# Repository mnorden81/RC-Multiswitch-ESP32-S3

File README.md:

# RC-Multiswitch-ESP32-S3

RC-Multiswitch mit 8 Schaltkanaelen auf einem Waveshare ESP32-S3-Zero.

Frueher `CRSF-Multiswitch-ESP32-S3`. Der neue Name ist neutral, weil der Multiswitch neben CRSF auch SBUS (UART A) als Eingang versteht.

Gleiche Funktion wie die C3-Variante, aber mit dem ESP32-S3-Zero und einem dritten UART. Das PCB wurde vom C3-Layout uebernommen, die Leitungen am ESP32 sind neu verlegt (DRC steht noch aus).

Dokumente:
- [docs/Projektbeschreibung.docx](docs/Projektbeschreibung.docx): Projektbeschreibung
- [docs/Hardware-Beschreibung_C3_S3.docx](docs/Hardware-Beschreibung_C3_S3.docx): Hardware-Beschreibung C3 und S3 (Stecker, Kanalzuordnung, Stueckliste, Dimensionierung)
- [docs/Abnahmepruefung.md](docs/Abnahmepruefung.md): Abnahmepruefung (Pruefliste fuer ein fertig gebautes Modul)
- [docs/Firmware-Spezifikation.md](docs/Firmware-Spezifikation.md) (auch als DOCX): Firmware-Spezifikation (Basis V3, Router fuer Modulketten, BOOT-Taster, Status-LED)

## Merkmale
- 8 Schaltkanaele ueber TBD62083APG (negativ) oder TBD62783APG (positiv), Kontroll-LED je Kanal
- UART A (Eingang), UART B und UART C mit waehlbarer Rolle: Modulkette (CRSF), S.Port-LiPo-Sensoren, GPS oder Raw, je mit eigener Baudrate
- Versorgung des ESP32 aus +5 V des Empfaengers, Last getrennt mit 5-12 V
- Eigener THT-Footprint fuer den S3-Zero (nur 2x9 Header)

## Hardware (v0.4 (PCB vom C3 uebertragen))
Board: Waveshare ESP32-S3-Zero

- Lastspannung 5-12 V (VLOAD) an CN2 (JST PH 2), TVS-Diode P6KE18A als Schutz.
- Treiber TBD62083APG (DMOS, Nachfolger des ULN2803A, gleiche Pinbelegung; ein ULN2803A passt weiterhin in den Sockel), 8 Kanaele, max. 500 mA je Kanal, Summe aller Kanaele ca. 1,5 A. Spannungsabfall am Ausgang nur ca. 0,2-0,4 V statt ca. 1 V beim ULN2803A. Positiv schaltende Variante mit TBD62783APG siehe [hardware/README-hardware.md](hardware/README-hardware.md).
- R9-R16 (THT 1/4 W) zwischen Treiber-Ausgang und Stiftleiste J1: kein Wert vorgegeben, der Anwender legt sie passend zu Verbraucher und Lastspannung aus.
- R1-R8 und LED1-LED8 (3 mm) als Kontroll-LED je Kanal, vom Steuersignal Sn gegen GND. Werte legt der Anwender fest, eine Empfehlung ist auf der Platine aufgedruckt.
- Keine Pulldowns und keine Widerstaende in den UART-Leitungen. Der ESP32 wird aus +5 V von CN1 (BEC/Empfaenger) versorgt.

### Belegung
| Funktion | GPIO |
|---|---|
| S0..S7 | IO11, IO4, IO5, IO6, IO10, IO9, IO8, IO7 |
| UART A (CN1, Eingang) | TX IO43, RX IO44 (UART0) |
| UART B (J5) | TX IO13, RX IO12 |
| UART C (J6) | TX IO2, RX IO1 |
| Frei | IO3 (Strapping), IO14-IO16 (Loetpads) |

### Anschluesse
- CN1, J5, J6: UART A/B/C als JST-GH 4 (Footprint BM04B-GHS-TBT)
- CN2 Last 5-12 V (JST PH 2, max. ca. 2 A je Kontakt)
- J1 Ausgaenge S0..S7

### Hinweise
- UART A liegt auf UART0: beim Booten gibt das ROM ein Log auf IO43 aus.
- Empfehlung LED-Vorwiderstaende R1-R8 bei 3,3 V (ca. 5 mA, auch auf der Platine aufgedruckt): Rot/Gelb 270 R, Gruen 220 R, Blau/Weiss 56 R.
- Footprint ESP32-S3-Zero_THT: 2x9, 2,54 mm, Reihenabstand 15,24 mm. Vor dem Layout 1:1 am echten Board pruefen.

## Firmware (v4.09)
- Arduino-Sketch `firmware/RC_Multiswitch`, gleicher Quellcode fuer C3 und S3 (Board wird automatisch erkannt). Basis: MultiSwitch_ESP32_V3 v3.12.
- CRSF auf UART A (Werkseinstellung ab v4.07), wahlweise SBUS. UART B und UART C per Lua oder Web-UI auf Aus, CRSF (Modulkette), S.Port, GPS oder Raw einstellbar, mit eigener Baudrate je UART. Beim GPS sucht die Baudrate „Auto“ (Vorgabe) die Rate selbst und stellt das GPS auf 115200 Baud und 10 Hz um, wie bei Betaflight. In der Modulkette ist jedes Modul mit eigener Adresse ueber Lua einzeln einstellbar. Lua-Menü ab v4.09: Ordner zeigen ihren Wert (z. B. „Ausgang 1 (Kanal_L 5)“), Felder ohne Wirkung werden ausgeblendet.
- Gemeinsame Basis aller ESP32-Module seit v4.05: `firmware/RC_Multiswitch/src/RC_Common/` (siehe deren README).
- BOOT-Taster 3 s: WLAN-AP ein/aus. Status-LED nur beim S3.
- Details und Bauanleitung: [firmware/README.md](firmware/README.md).

## Firmware flashen

Es gibt drei Wege. Ein neues Modul wird einmal per USB geflasht (Weg 1 oder Weg 2), danach geht jedes Update bequem per WLAN (Weg 3).

| Weg | Braucht | Einstellungen im Modul |
|---|---|---|
| 1. Fertige Datei aus GitHub + Web-Flasher | nur Chrome oder Edge | werden **gelöscht** |
| 2. Arduino IDE | Arduino IDE 2.x | bleiben erhalten |
| 3. Update per WLAN | Handy oder PC mit WLAN | bleiben erhalten |

Der Sketch ist für C3 und S3 derselbe, das Board wird automatisch erkannt. Für dieses Repo (Waveshare ESP32-S3-Zero) gilt das Artefakt `RC_Multiswitch-S3` und die Einstellungen unten.

### Weg 1: Fertige Firmware aus GitHub (ohne Arduino IDE)

GitHub baut die Firmware bei jeder Änderung automatisch (Workflow „Firmware bauen“).

1. Auf GitHub angemeldet sein (sonst gibt es keinen Download-Knopf).
2. In diesem Repo oben auf **Actions** klicken, links den Workflow **Firmware bauen** wählen.
3. Den obersten Lauf mit grünem Haken öffnen (Branch `main`).
4. Ganz unten unter **Artifacts** **RC_Multiswitch-S3** herunterladen und die ZIP-Datei entpacken. Darin liegen u. a. `RC_Multiswitch.ino.merged.bin` (Komplett-Image für USB) und `RC_Multiswitch.ino.bin` (nur für Weg 3).
   Steht dort nichts (Artefakte werden nach 90 Tagen gelöscht): rechts oben **Run workflow** → **Run workflow** klicken, nach ca. 3 Minuten ist ein neuer Lauf fertig.
5. ESP32-S3-Zero mit einem USB-C-**Datenkabel** an den PC stecken (kein reines Ladekabel). Ein Treiber ist unter Windows 10/11 nicht nötig.
6. In **Chrome** oder **Edge** die Seite https://espressif.github.io/esptool-js/ öffnen (Espressif-Web-Flasher, Firefox geht nicht).
7. **Connect** klicken und den COM-Port des Moduls wählen. Klappt das nicht: Baudrate oben auf `115200` stellen und das Modul mit der BOOT-Taste in den Flash-Modus bringen (siehe Weg 2, „Wenn das Hochladen nicht klappt“).
8. Unter **Flash Address** `0x0` eintragen, mit **Datei auswählen** die `.merged.bin` wählen, dann **Program** klicken.
9. Wenn unten „Leaving…“ steht, das USB-Kabel kurz abziehen und wieder einstecken. Fertig.

> **Achtung:** Das Komplett-Image überschreibt den ganzen Flash (4 MB). Alle Einstellungen und die Sicherungen im Flash sind danach weg. Vorher in der Weboberfläche die Einstellungen als Datei sichern (Karte **Konfiguration sichern/wiederherstellen** → „Als Datei exportieren“) und hinterher dort wieder importieren. Wer die Einstellungen behalten will, nimmt Weg 2 oder 3.

### Weg 2: Arduino IDE

**Einmalig einrichten**

1. Arduino IDE 2.x installieren (https://www.arduino.cc/en/software).
2. **Datei → Einstellungen → Zusätzliche Boardverwalter-URLs**: `https://espressif.github.io/arduino-esp32/package_esp32_index.json` eintragen.
3. **Werkzeuge → Board → Boardverwalter**: „esp32“ suchen, **esp32 von Espressif Systems** in Version **3.0.7** installieren.
4. **Werkzeuge → Bibliotheken verwalten**: **Bolder Flight Systems SBUS 8.1.4**, **TinyGPSPlus 1.0.3** suchen und in genau dieser Version installieren.
   Alles andere (z. B. `src/RC_Common/`) liegt schon im Sketch-Ordner.

**Flashen**

1. Repo herunterladen: oben auf GitHub **Code → Download ZIP**, entpacken (oder den vorhandenen Ordner nehmen).
2. In der Arduino IDE **Datei → Öffnen** und `firmware/RC_Multiswitch/RC_Multiswitch.ino` wählen.
3. Unter **Werkzeuge** einstellen:

   | Einstellung | Wert |
   |---|---|
   | Board | **ESP32S3 Dev Module** |
   | USB CDC On Boot | **Enabled** (Pflicht, sonst Abbruch mit Meldung) |
   | Flash Size | 4MB (32Mb) |
   | Partition Scheme | **Default 4MB with spiffs (1.2MB APP/1.5MB SPIFFS)** |
   | PSRAM | Disabled |
   | Erase All Flash Before Sketch Upload | **Disabled** (sonst sind die Einstellungen weg) |

4. ESP32-S3-Zero mit einem USB-C-**Datenkabel** an den PC stecken (kein reines Ladekabel). Ein Treiber ist unter Windows 10/11 nicht nötig. Dann unter **Werkzeuge → Port** den neuen COM-Port wählen.
5. Auf den Pfeil **Hochladen** klicken. Am Ende steht „Hard resetting via RTS pin…“.
6. Das Modul startet von selbst neu. Wenn nicht: USB-Kabel kurz abziehen und wieder einstecken.

**Wenn das Hochladen nicht klappt** („Failed to connect“ oder „No serial data received“): USB abziehen, die Taste **BOOT** gedrückt halten, USB wieder einstecken, BOOT loslassen. Das Modul ist jetzt im Flash-Modus. Unter **Werkzeuge → Port** ggf. den neuen COM-Port wählen und noch einmal **Hochladen**. Danach das USB-Kabel einmal abziehen und wieder einstecken.

### Weg 3: Update per WLAN (OTA)

1. Die Datei `RC_Multiswitch.ino.bin` besorgen: aus GitHub (Weg 1, Schritte 1–4) oder in der Arduino IDE mit **Sketch → Kompilierte Binärdatei exportieren** (liegt dann im Sketch-Ordner unter `build/`). Nicht die `.merged.bin` nehmen.
2. WLAN des Moduls einschalten: BOOT-Taste 3 s halten (oder Lua „WLAN“ bzw. automatisch nach 60 s ohne RC-Signal). Name **MultiSwitch**, Passwort `123456789` (falls nicht geändert).
3. Mit Handy oder PC in dieses WLAN gehen und im Browser http://192.168.1.1 öffnen.
4. Reiter **WiFi**, Karte **Firmware-Update (OTA)**: die `.bin`-Datei auswählen und hochladen. Das Modul startet danach neu, die Einstellungen bleiben erhalten.

Schlägt das Update fehl, läuft die alte Firmware einfach weiter. Das Modul beim Update am besten über den Empfänger/BEC versorgen, nicht nur über einen schwachen USB-Anschluss.

## Ordner
- `hardware/`: KiCad-Projekt (Schaltplan, PCB, PDF, eigene Footprints, fp-lib-table). Entwurfsnotizen in [hardware/README-hardware.md](hardware/README-hardware.md). 3D-druckbares Gehaeuse in [hardware/gehaeuse/](hardware/gehaeuse/README.md).
- `firmware/`: Firmware v4.09 (Arduino-Sketch).
- `docs/`: Projektbeschreibung, Hardware-Beschreibung und Firmware-Spezifikation.

## Stand
- Hardware: Schaltplan fertig, PCB vom C3 uebernommen und an U1 neu verlegt. DRC in KiCad steht noch aus, J6 nur vorlaeufig platziert.
- Firmware: v4.09 kompiliert fuer C3 und S3, noch nicht auf Hardware getestet.

## Offene Punkte
- DRC in KiCad ausfuehren (an U1 sind laut PCB-Datei alle Anschluesse verlegt)
- Platzierung von J6 (UART C) festlegen
- Footprint am echten Board pruefen
- Firmware auf Hardware testen (Einzelmodul und Kette mit 2-3 Modulen)

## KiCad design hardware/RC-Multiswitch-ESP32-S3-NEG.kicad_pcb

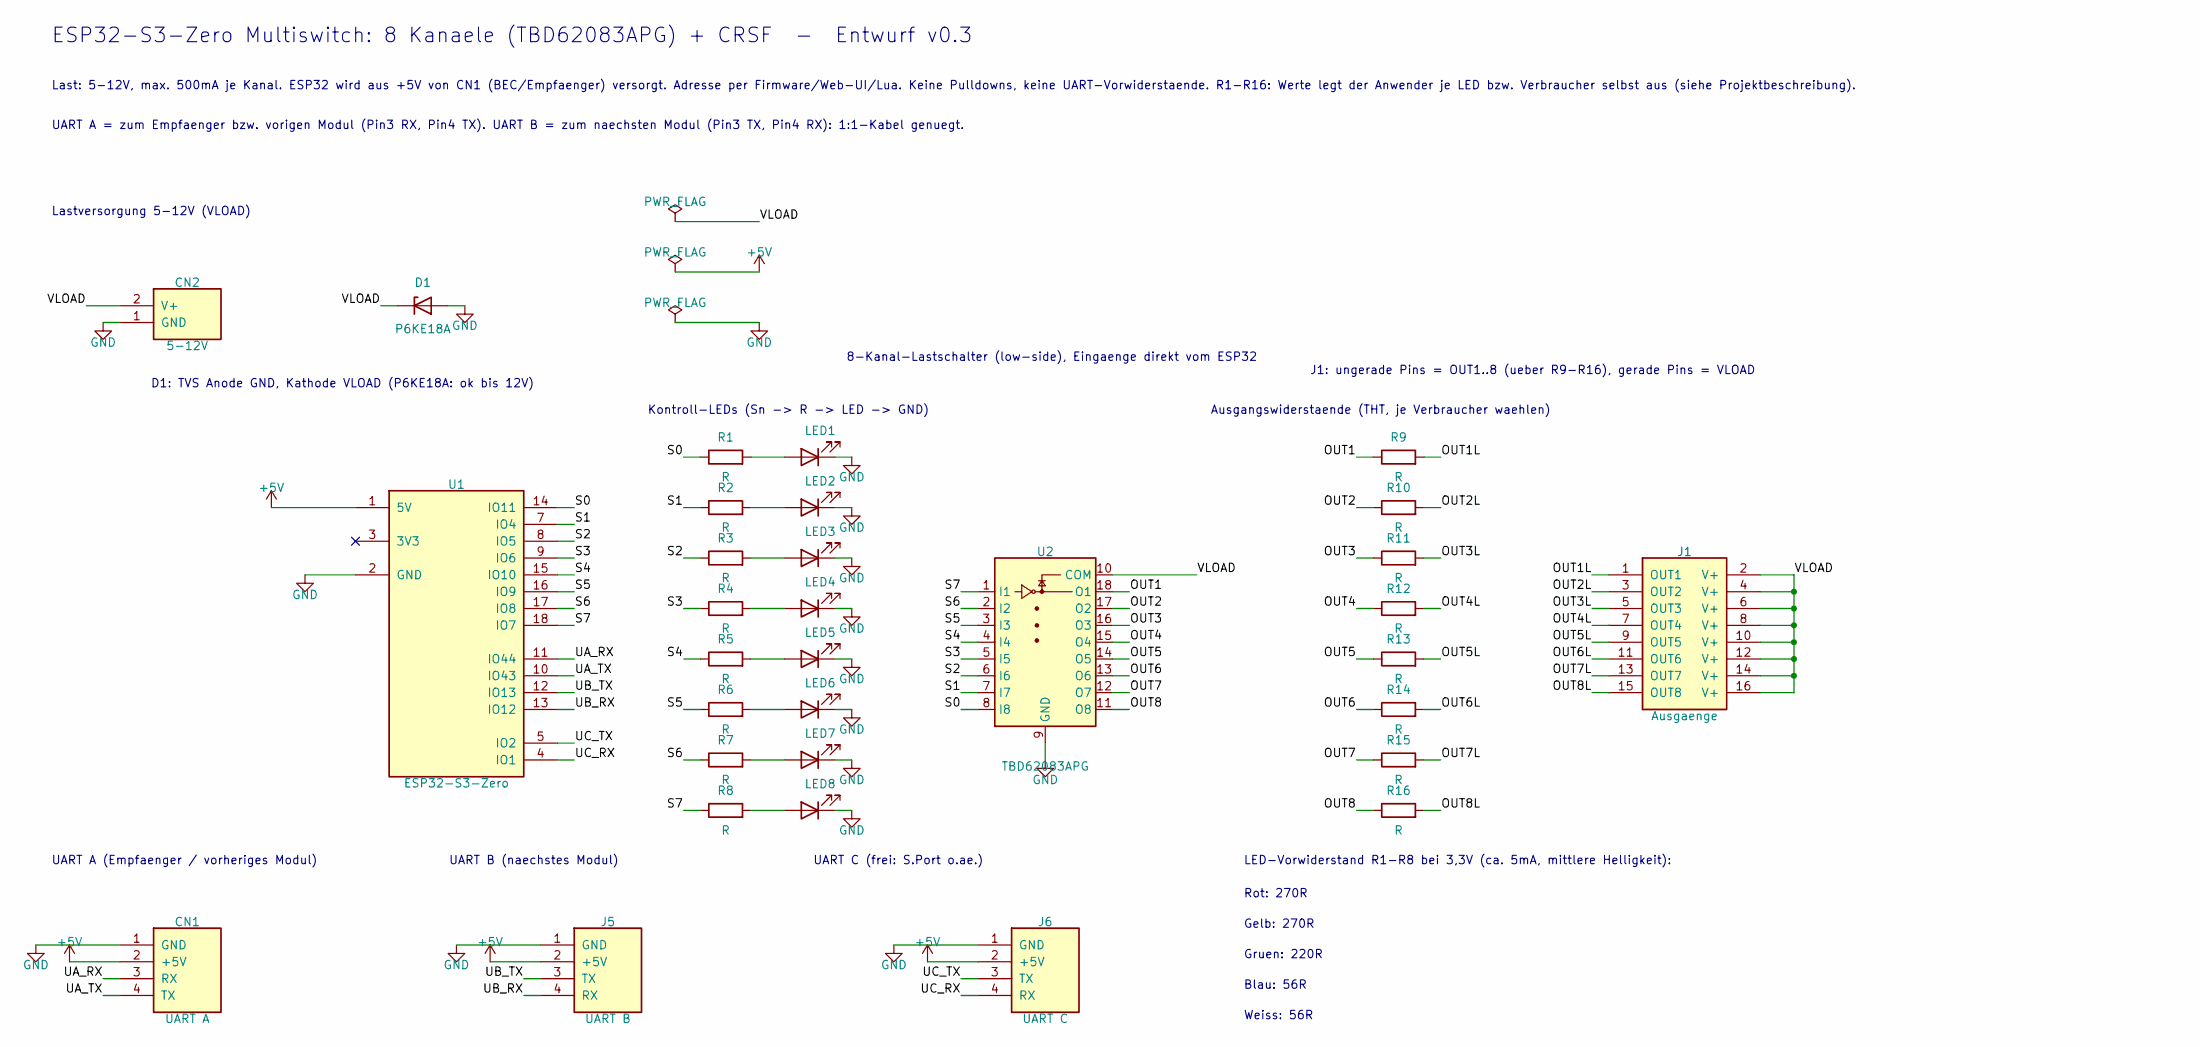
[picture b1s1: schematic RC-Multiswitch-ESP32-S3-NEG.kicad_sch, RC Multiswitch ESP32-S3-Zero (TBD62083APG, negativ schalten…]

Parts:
CN1: UART A; JST_PH_S4B-PH-K_1x04_P2.00mm_Horizontal
CN2: 5-12V; JST_PH_S2B-PH-K_1x02_P2.00mm_Horizontal
D1: P6KE18A; D_DO-15_P12.70mm_Horizontal
J1: Ausgaenge; PinHeader_2x08_P2.54mm_Vertical
J5: UART B; JST_PH_S4B-PH-K_1x04_P2.00mm_Horizontal
J6: UART C; JST_PH_S4B-PH-K_1x04_P2.00mm_Horizontal
LED1, LED2, LED3, LED4, LED5, LED6, LED7, LED8: LED; LED_D3.0mm
R1, R2, R3, R4, R5, R6, R7, R8, R9, R10, R11, R12, R13, R14, R15, R16: R; R_Axial_DIN0207_L6.3mm_D2.5mm_P7.62mm_Horizontal
U1: ESP32-S3-Zero; ESP32-S3-Zero_THT
U2: TBD62083APG; DIP-18_W7.62mm_Socket

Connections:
+5V: CN1.2 (+5V), J5.2 (+5V), J6.2 (+5V), U1.1 (5V)
/OUT1: R9.1, U2.18 (O1)
/OUT1L: J1.1 (OUT1), R9.2
/OUT2: R10.1, U2.17 (O2)
/OUT2L: J1.3 (OUT2), R10.2
/OUT3: R11.1, U2.16 (O3)
/OUT3L: J1.5 (OUT3), R11.2
/OUT4: R12.1, U2.15 (O4)
/OUT4L: J1.7 (OUT4), R12.2
/OUT5: R13.1, U2.14 (O5)
/OUT5L: J1.9 (OUT5), R13.2
/OUT6: R14.1, U2.13 (O6)
/OUT6L: J1.11 (OUT6), R14.2
/OUT7: R15.1, U2.12 (O7)
/OUT7L: J1.13 (OUT7), R15.2
/OUT8: R16.1, U2.11 (O8)
/OUT8L: J1.15 (OUT8), R16.2
/S0: R1.1, U1.14 (IO11), U2.8 (I8)
/S1: R2.1, U1.7 (IO4), U2.7 (I7)
/S2: R3.1, U1.8 (IO5), U2.6 (I6)
/S3: R4.1, U1.9 (IO6), U2.5 (I5)
/S4: R5.1, U1.15 (IO10), U2.4 (I4)
/S5: R6.1, U1.16 (IO9), U2.3 (I3)
/S6: R7.1, U1.17 (IO8), U2.2 (I2)
/S7: R8.1, U1.18 (IO7), U2.1 (I1)
/UA_RX: CN1.3 (RX), U1.11 (IO44)
/UA_TX: CN1.4 (TX), U1.10 (IO43)
/UB_RX: J5.4 (RX), U1.13 (IO12)
/UB_TX: J5.3 (TX), U1.12 (IO13)
/UC_RX: J6.4 (RX), U1.4 (IO1)
/UC_TX: J6.3 (TX), U1.5 (IO2)
/VLOAD: CN2.2 (V+), D1.1 (K), J1.2 (V+), J1.4 (V+), J1.6 (V+), J1.8 (V+), J1.10 (V+), J1.12 (V+), J1.14 (V+), J1.16 (V+), U2.10 (COM)
GND: CN1.1 (GND), CN2.1 (GND), D1.2 (A), J5.1 (GND), J6.1 (GND), LED1.1 (K), LED2.1 (K), LED3.1 (K), LED4.1 (K), LED5.1 (K), LED6.1 (K), LED7.1 (K), LED8.1 (K), U1.2 (GND), U2.9 (GND)
unnamed: LED1.2 (A), R1.2
unnamed: LED2.2 (A), R2.2
unnamed: LED3.2 (A), R3.2
unnamed: LED4.2 (A), R4.2
unnamed: LED5.2 (A), R5.2
unnamed: LED6.2 (A), R6.2
unnamed: LED7.2 (A), R7.2
unnamed: LED8.2 (A), R8.2

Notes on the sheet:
Gruen: 220R
D1: TVS Anode GND, Kathode VLOAD (P6KE18A: ok bis 12V)
UART A = zum Empfaenger bzw. vorigen Modul (Pin3 RX, Pin4 TX). UART B = zum naechsten Modul (Pin3 TX, Pin4 RX): 1:1-Kabel genuegt.
Lastversorgung 5-12V (VLOAD)
Ausgangswiderstaende (THT, je Verbraucher waehlen)
8-Kanal-Lastschalter (low-side), Eingaenge direkt vom ESP32
J1: ungerade Pins = OUT1..8 (ueber R9-R16), gerade Pins = VLOAD
Rot: 270R
UART C (frei: S.Port o.ae.)
Kontroll-LEDs (Sn -> R -> LED -> GND)
LED-Vorwiderstand R1-R8 bei 3,3V (ca. 5mA, mittlere Helligkeit):
Weiss: 56R
Last: 5-12V, max. 500mA je Kanal. ESP32 wird aus +5V von CN1 (BEC/Empfaenger) versorgt. Adresse per Firmware/Web-UI/Lua. Keine Pulldowns, keine UART-Vorwiderstaende. R1-R16: Werte legt der Anwender je LED bzw. Verbraucher selbst aus (siehe Projektbeschreibung).
ESP32-S3-Zero Multiswitch: 8 Kanaele (TBD62083APG) + CRSF - Entwurf v0.3
Blau: 56R
Gelb: 270R
UART B (naechstes Modul)
UART A (Empfaenger / vorheriges Modul)

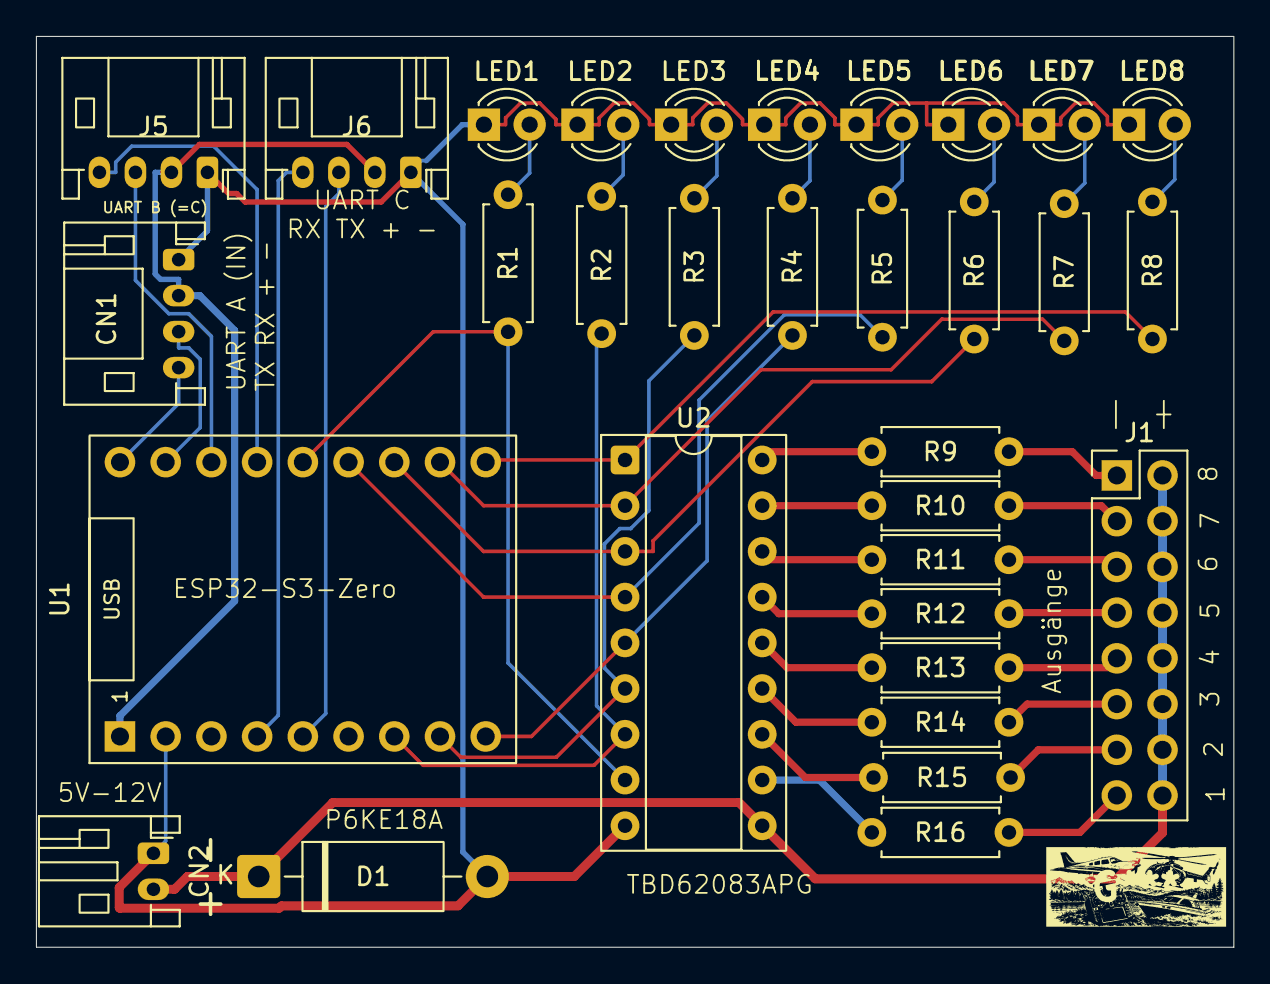
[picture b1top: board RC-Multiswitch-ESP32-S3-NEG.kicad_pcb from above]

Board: 2 copper layers, 66.5 x 50.6 mm, 32 parts (0 on the bottom side), 41 nets.
